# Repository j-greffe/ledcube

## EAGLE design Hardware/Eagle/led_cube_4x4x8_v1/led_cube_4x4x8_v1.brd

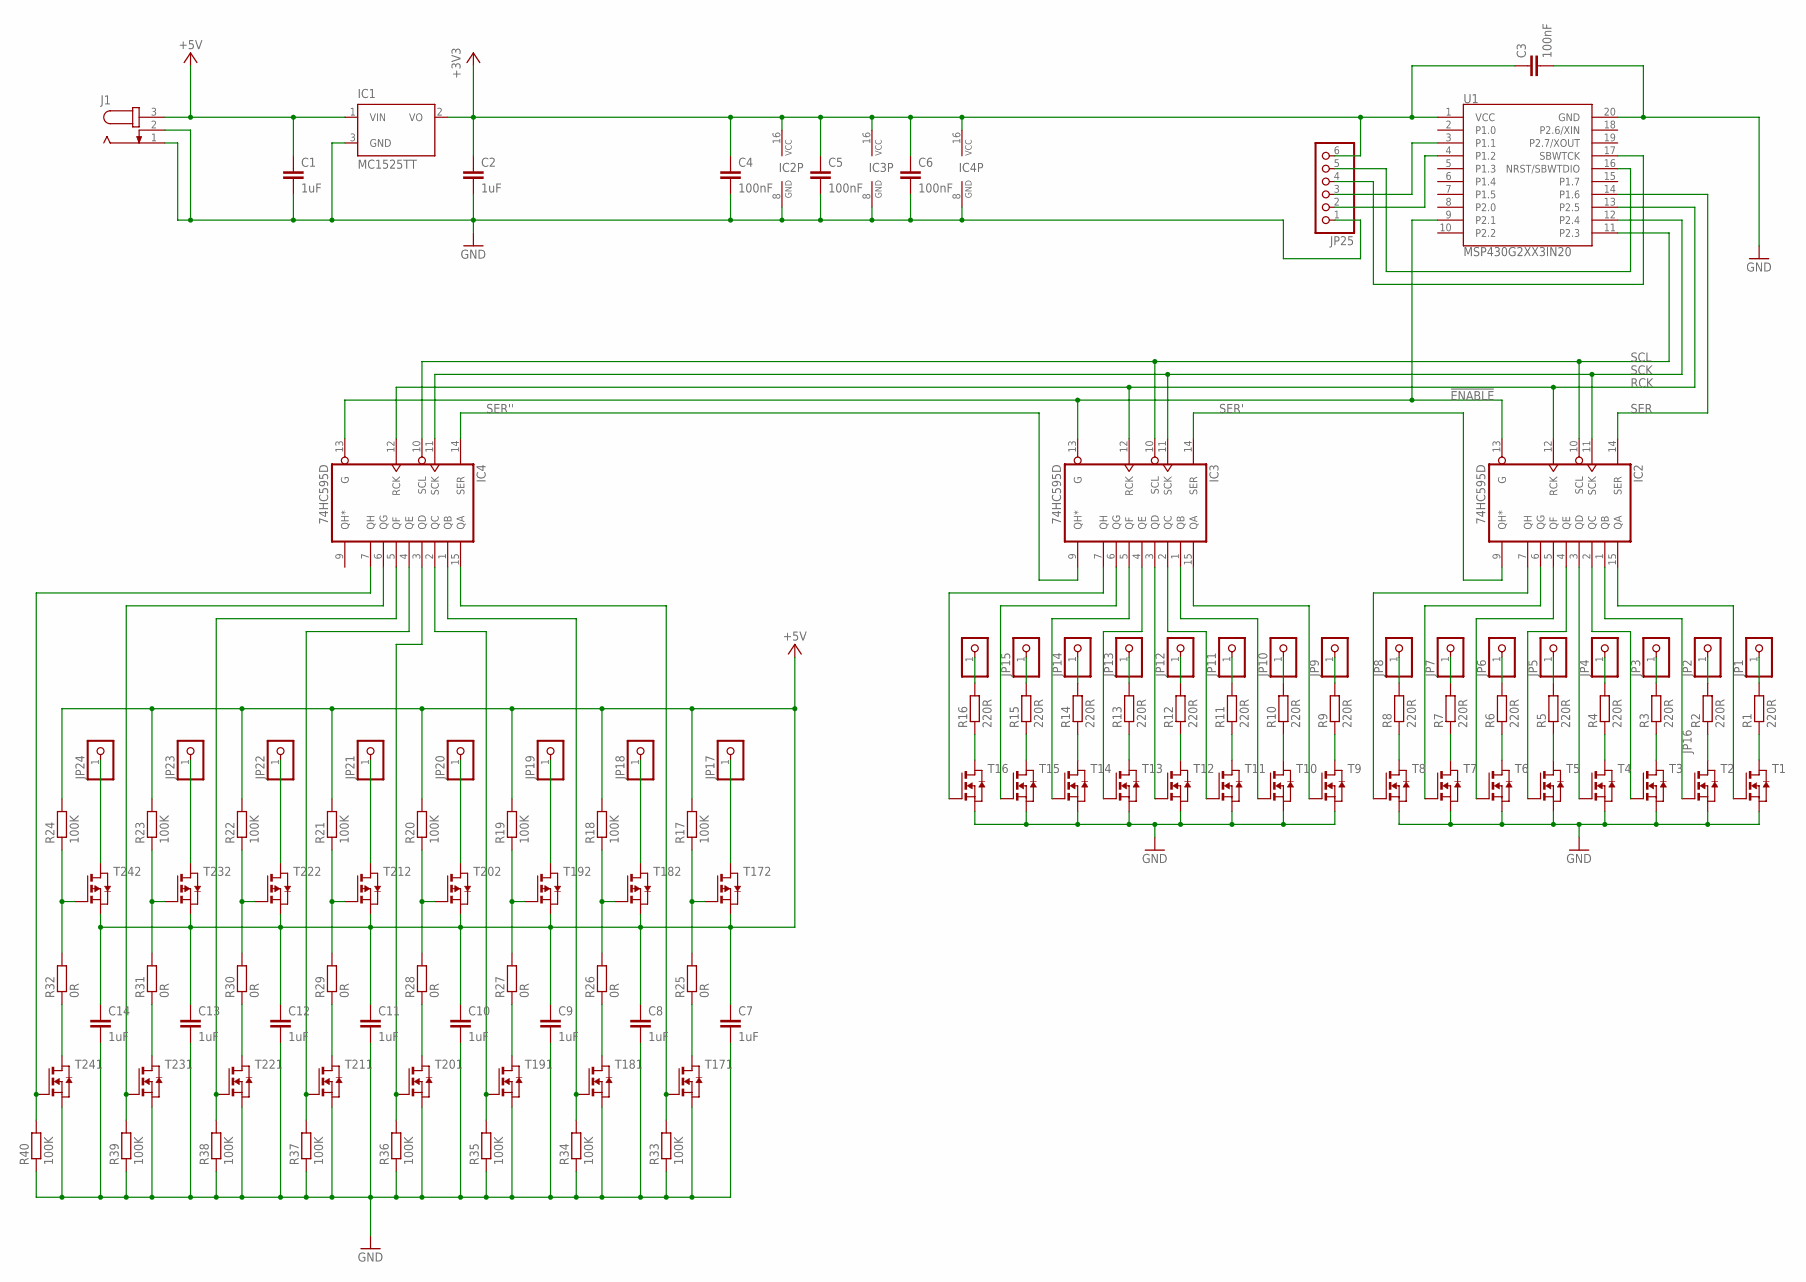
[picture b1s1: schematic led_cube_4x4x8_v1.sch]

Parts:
C1, C2, C7, C8, C9, C10, C11, C12, C13, C14: 1uF; C0603
C3, C4, C5, C6: 100nF; C0603
IC1: MC1525TT; SOT23
IC2, IC3, IC4: 74HC595D; SO16
J1: JACK-PLUG0; SPC4077
JP1, JP2, JP3, JP4, JP5, JP6, JP7, JP8, JP9, JP10, JP11, JP12, JP13, JP14, JP15, JP16, JP17, JP18, JP19, JP20, JP21, JP22, JP23, JP24: PINHD-1X1; 1X01
JP25: PINHD-1X6; 1X06
R1, R2, R3, R4, R5, R6, R7, R8, R9, R10, R11, R12, R13, R14, R15, R16: 220R; R0603
R17, R18, R19, R20, R21, R22, R23, R24, R33, R34, R35, R36, R37, R38, R39, R40: 100K; R0603
R25, R26, R27, R28, R29, R30, R31, R32: 0R; R0603
T1, T2, T3, T4, T5, T6, T7, T8, T9, T10, T11, T12, T13, T14, T15, T16: NMOSSOT23; SOT-23
T17, T18, T19, T20, T21, T22, T23, T24: PN_MOSFET-SOT23-6; SOT23-6
U1: MSP430G2XX3IN20; DIL20

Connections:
!ENABLE: IC2.13 (G), IC3.13 (G), IC4.13 (G), U1.9 (P2.1)
+3V3: C2.1, C3.1, C4.1, C5.1, C6.1, IC1.2 (VO), IC2.16 (VCC), IC3.16 (VCC), IC4.16 (VCC), JP25.6, U1.1 (VCC)
+5V: C1.1, C7.1, C8.1, C9.1, C10.1, C11.1, C12.1, C13.1, C14.1, IC1.1 (VIN), J1.3, R17.2, R18.2, R19.2, R20.2, R21.2, R22.2, R23.2, R24.2, T17.2 (S), T18.2 (S), T19.2 (S), T20.2 (S), T21.2 (S), T22.2 (S), T23.2 (S), T24.2 (S)
GND: C1.2, C2.2, C3.2, C4.2, C5.2, C6.2, C7.2, C8.2, C9.2, C10.2, C11.2, C12.2, C13.2, C14.2, IC1.3 (GND), IC2.8 (GND), IC3.8 (GND), IC4.8 (GND), J1.1, J1.2, JP25.1, R33.1, R34.1, R35.1, R36.1, R37.1, R38.1, R39.1, R40.1, T1.2 (S), T2.2 (S), T3.2 (S), T4.2 (S), T5.2 (S), T6.2 (S), T7.2 (S), T8.2 (S), T9.2 (S), T10.2 (S), T11.2 (S), T12.2 (S), T13.2 (S), T14.2 (S), T15.2 (S), T16.2 (S), T17.5 (S), T18.5 (S), T19.5 (S), T20.5 (S), T21.5 (S), T22.5 (S), T23.5 (S), T24.5 (S), U1.20 (GND)
unnamed: R22.1, R30.2, T22.3 (G)
unnamed: R8.1, T8.1 (D)
unnamed: R7.1, T7.1 (D)
unnamed: R6.1, T6.1 (D)
unnamed: R5.1, T5.1 (D)
unnamed: R4.1, T4.1 (D)
unnamed: R3.1, T3.1 (D)
unnamed: R2.1, T2.1 (D)
unnamed: R1.1, T1.1 (D)
unnamed: IC2.6 (QG), T7.3 (G)
unnamed: IC2.7 (QH), T8.3 (G)
unnamed: IC2.5 (QF), T6.3 (G)
unnamed: IC2.4 (QE), T5.3 (G)
unnamed: IC2.3 (QD), T4.3 (G)
unnamed: IC2.2 (QC), T3.3 (G)
unnamed: IC2.1 (QB), T2.3 (G)
unnamed: IC2.15 (QA), T1.3 (G)
unnamed: JP8.1, R8.2
unnamed: JP7.1, R7.2
unnamed: JP6.1, R6.2
unnamed: JP5.1, R5.2
unnamed: JP4.1, R4.2
unnamed: JP3.1, R3.2
unnamed: JP2.1, R2.2
unnamed: JP1.1, R1.2
unnamed: R16.1, T16.1 (D)
unnamed: R15.1, T15.1 (D)
unnamed: R14.1, T14.1 (D)
unnamed: R13.1, T13.1 (D)
unnamed: R12.1, T12.1 (D)
unnamed: R11.1, T11.1 (D)
unnamed: R10.1, T10.1 (D)
unnamed: R9.1, T9.1 (D)
unnamed: IC3.6 (QG), T15.3 (G)
unnamed: IC3.7 (QH), T16.3 (G)
unnamed: IC3.5 (QF), T14.3 (G)
unnamed: IC3.4 (QE), T13.3 (G)
unnamed: IC3.3 (QD), T12.3 (G)
unnamed: IC3.2 (QC), T11.3 (G)
unnamed: IC3.1 (QB), T10.3 (G)
unnamed: IC3.15 (QA), T9.3 (G)
unnamed: JP16.1, R16.2
unnamed: JP15.1, R15.2
unnamed: JP14.1, R14.2
unnamed: JP13.1, R13.2
unnamed: JP12.1, R12.2
unnamed: JP11.1, R11.2
unnamed: JP10.1, R10.2
unnamed: JP9.1, R9.2
unnamed: R23.1, R31.2, T23.3 (G)
unnamed: R21.1, R29.2, T21.3 (G)
unnamed: R20.1, R28.2, T20.3 (G)
unnamed: R19.1, R27.2, T19.3 (G)
unnamed: R18.1, R26.2, T18.3 (G)
unnamed: R17.1, R25.2, T17.3 (G)
unnamed: JP24.1, T24.4 (D)
unnamed: JP23.1, T23.4 (D)
unnamed: IC4.7 (QH), R40.2, T24.1 (G)
unnamed: JP22.1, T22.4 (D)
unnamed: JP21.1, T21.4 (D)
unnamed: JP20.1, T20.4 (D)
unnamed: JP19.1, T19.4 (D)
unnamed: JP18.1, T18.4 (D)
unnamed: JP17.1, T17.4 (D)
unnamed: IC4.3 (QD), R36.2, T20.1 (G)
unnamed: R24.1, R32.2, T24.3 (G)
unnamed: IC4.6 (QG), R39.2, T23.1 (G)
unnamed: IC4.5 (QF), R38.2, T22.1 (G)
unnamed: IC4.4 (QE), R37.2, T21.1 (G)
unnamed: R32.1, T24.6 (D)
unnamed: IC4.2 (QC), R35.2, T19.1 (G)
unnamed: IC4.1 (QB), R34.2, T18.1 (G)
unnamed: IC4.15 (QA), R33.2, T17.1 (G)
unnamed: JP25.2, U1.4 (P1.2)
unnamed: JP25.3, U1.3 (P1.1)
unnamed: JP25.4, U1.17 (SBWTCK)
unnamed: JP25.5, U1.16 (NRST/SBWTDIO)
unnamed: R31.1, T23.6 (D)
unnamed: R30.1, T22.6 (D)
unnamed: R29.1, T21.6 (D)
unnamed: R28.1, T20.6 (D)
unnamed: R27.1, T19.6 (D)
unnamed: R26.1, T18.6 (D)
unnamed: R25.1, T17.6 (D)
RCK: IC2.12 (RCK), IC3.12 (RCK), IC4.12 (RCK), U1.13 (P2.5)
SCK: IC2.11 (SCK), IC3.11 (SCK), IC4.11 (SCK), U1.12 (P2.4)
SCL: IC2.10 (SCL), IC3.10 (SCL), IC4.10 (SCL), U1.11 (P2.3)
SER: IC2.14 (SER), U1.14 (P1.6)
SER': IC2.9 (QH*), IC3.14 (SER)
SER'': IC3.9 (QH*), IC4.14 (SER)

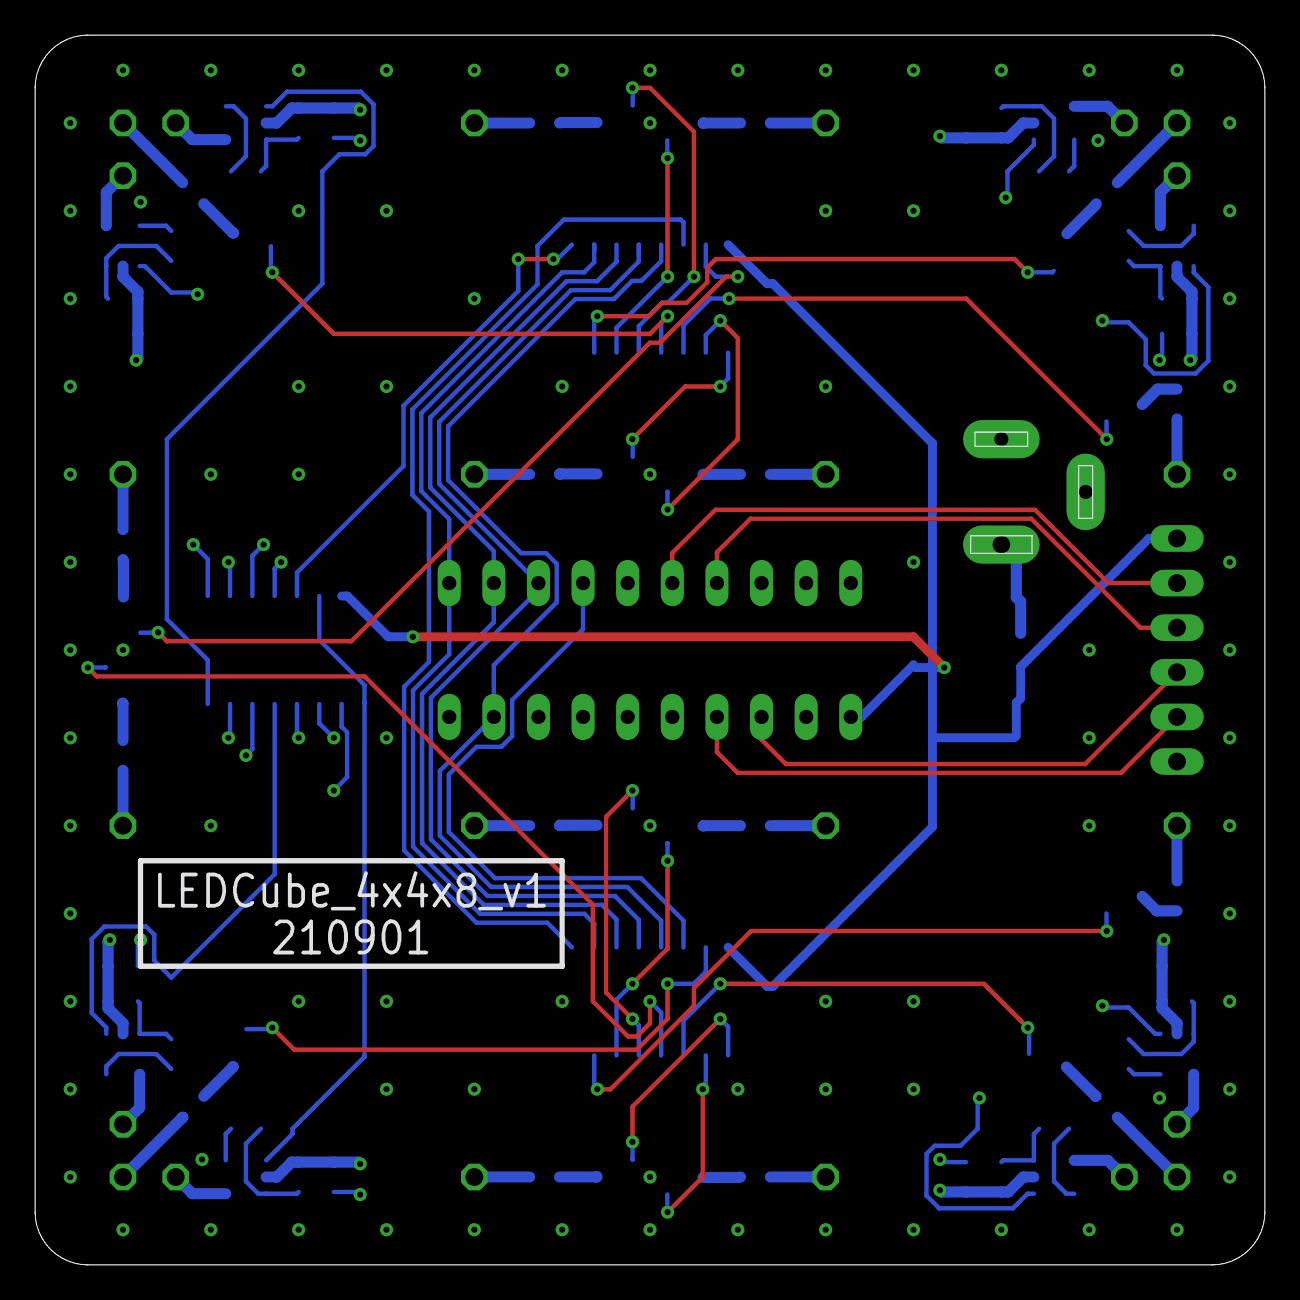
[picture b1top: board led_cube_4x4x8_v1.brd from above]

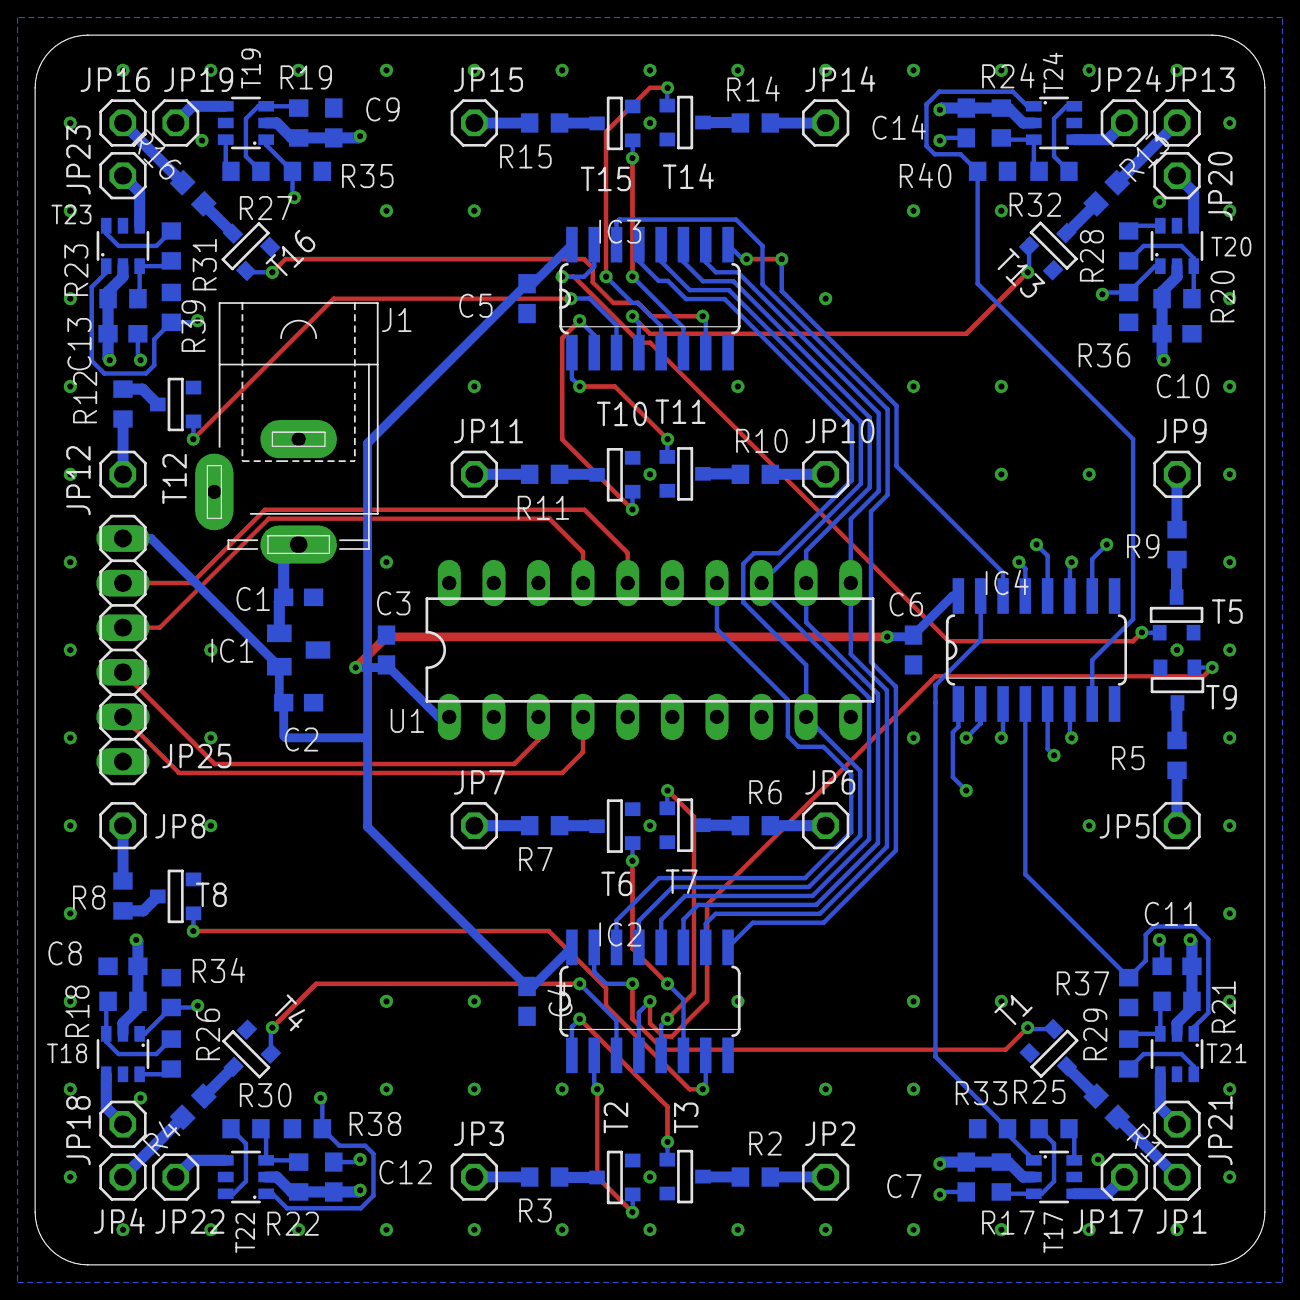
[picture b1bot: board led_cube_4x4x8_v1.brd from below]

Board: 4 copper layers, 70.0 x 70.0 mm, 109 parts (109 on the bottom side), 94 nets.

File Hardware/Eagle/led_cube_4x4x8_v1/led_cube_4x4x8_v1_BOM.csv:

"Qty";"Value";"Device";"Package";"Parts";"Description";"MF";"MPN";"OC_FARNELL";"OC_NEWARK";"POPULARITY";"SPICEPREFIX";
"1";"";"JACK-PLUG0";"SPC4077";"J1";"DC POWER JACK";"";"";"unknown";"unknown";"0";"";
"16";"";"NMOSSOT23";"SOT-23";"T1, T2, T3, T4, T5, T6, T7, T8, T9, T10, T11, T12, T13, T14, T15, T16";"MOS FET";"";"";"unknown";"unknown";"5";"";
"24";"";"PINHD-1X1";"1X01";"JP1, JP2, JP3, JP4, JP5, JP6, JP7, JP8, JP9, JP10, JP11, JP12, JP13, JP14, JP15, JP16, JP17, JP18, JP19, JP20, JP21, JP22, JP23, JP24";"PIN HEADER";"";"";"";"";"64";"";
"1";"";"PINHD-1X6";"1X06";"JP25";"PIN HEADER";"";"";"";"";"79";"";
"8";"";"PN_MOSFET-SOT23-6";"SOT23-6";"T17, T18, T19, T20, T21, T22, T23, T24";"DUAL N AND P-CHANNEL ENHANCEMENT MODE MOSFET";"";"";"";"";"";"";
"8";"0R";"R-EU_R0603";"R0603";"R25, R26, R27, R28, R29, R30, R31, R32";"RESISTOR, European symbol";"";"";"";"";"70";"R";
"16";"100K";"R-EU_R0603";"R0603";"R17, R18, R19, R20, R21, R22, R23, R24, R33, R34, R35, R36, R37, R38, R39, R40";"RESISTOR, European symbol";"";"";"";"";"70";"R";
"4";"100nF";"C-EUC0603";"C0603";"C3, C4, C5, C6";"CAPACITOR, European symbol";"";"";"";"";"73";"C";
"10";"1uF";"C-EUC0603";"C0603";"C1, C2, C7, C8, C9, C10, C11, C12, C13, C14";"CAPACITOR, European symbol";"";"";"";"";"73";"C";
"16";"220R";"R-EU_R0603";"R0603";"R1, R2, R3, R4, R5, R6, R7, R8, R9, R10, R11, R12, R13, R14, R15, R16";"RESISTOR, European symbol";"";"";"";"";"70";"R";
"3";"74HC595D";"74HC595D";"SO16";"IC2, IC3, IC4";"8-bit SHIFT REGISTER, output latch";"";"";"";"";"21";"";
"1";"MC1525TT";"MC1525TT";"SOT23";"IC1";"2.5V and 4.096V Voltage References";"";"";"unknown";"unknown";"0";"";
"1";"MSP430G2XX3IN20";"MSP430G2XX3IN20";"DIL20";"U1";"";"";"";"";"";"";"";

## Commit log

2020-11-15 Initial commit.
2020-11-24 Use gpio_t instead of pointer. Added void io def HAL_IO_NONE. Check if io is void and do nothing if it is.
2020-11-28 Added clock module. Added return codes to hal_pwm.c
2021-09-03 Cleanup
2021-09-11 Added Hardware files.
2021-09-11 Moved Software.
2021-09-18 Implemented some animations.
